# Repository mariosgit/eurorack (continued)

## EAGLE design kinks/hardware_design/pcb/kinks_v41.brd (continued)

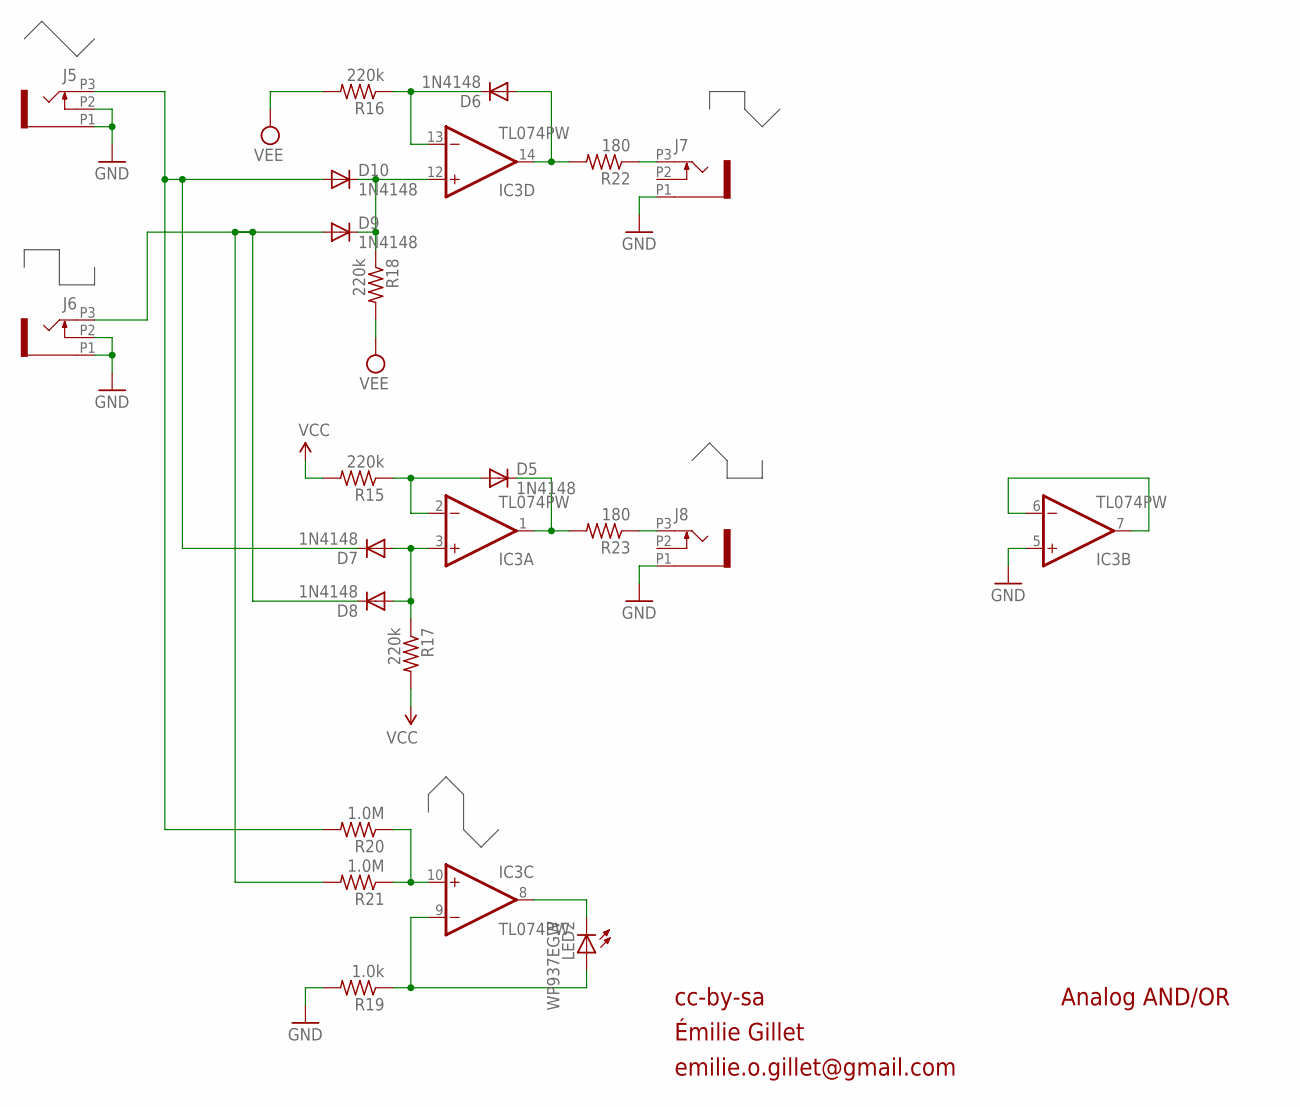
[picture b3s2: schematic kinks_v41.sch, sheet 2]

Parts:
D5, D6, D7, D8, D9, D10: 1N4148; SOD523
IC3: TL074PW; TSSOP14
J5, J6, J7, J8: PJ301_THONKICONN6; WQP_PJ_301M6
LED2: WP937EGW; LED3MM
R15, R16, R17, R18: 220k; R0402
R19: 1.0k; R0402
R20, R21: 1.0M; R0402
R22, R23: 180; R0402

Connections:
A: D7.C, D10.A, J5.P3 (3), R20.2
B: D8.C, D9.A, J6.P3 (3), R21.2
GND: IC3.5 (+IN), J5.P1 (1), J5.P2 (2), J6.P1 (1), J6.P2 (2), J7.P1 (1), J8.P1 (1), R19.2; also elsewhere on the board
unnamed: D9.C, D10.C, IC3.12 (+IN), R18.1
unnamed: D6.A, IC3.14 (OUT), R22.2
unnamed: D6.C, IC3.13 (-IN), R16.1
unnamed: D7.A, D8.A, IC3.3 (+IN), R17.1
unnamed: IC3.6 (-IN), IC3.7 (OUT)
unnamed: D5.C, IC3.1 (OUT), R23.2
unnamed: IC3.8 (OUT), LED2.K (C)
unnamed: D5.A, IC3.2 (-IN), R15.1
unnamed: J8.P3 (3), R23.1
unnamed: IC3.10 (+IN), R20.1, R21.1
unnamed: IC3.9 (-IN), LED2.A, R19.1
unnamed: J7.P3 (3), R22.1
VCC: R15.2, R17.2; also elsewhere on the board
VEE: R16.2, R18.2; also elsewhere on the board

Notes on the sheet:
cc-by-sa
Analog AND/OR
Émilie Gillet
emilie.o.gillet@gmail.com

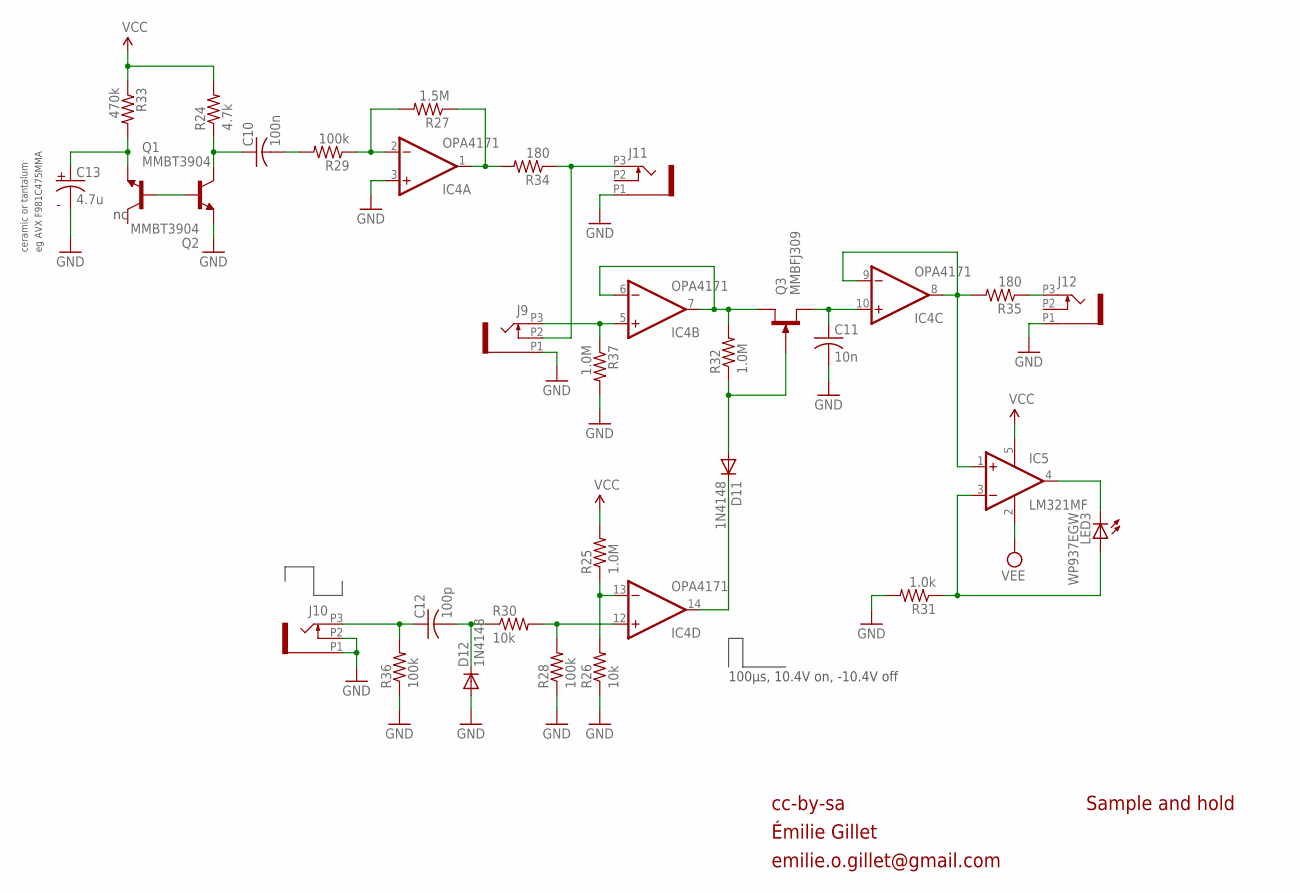
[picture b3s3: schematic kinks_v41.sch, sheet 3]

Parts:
C10: 100n; C0402
C11: 10n; C0603
C12: 100p; C0402
C13: 4.7u; C0603
D11, D12: 1N4148; SOD523
IC4: OPA4171; TSSOP14
IC5: LM321MF; SOT23-5
J9, J10, J11, J12: PJ301_THONKICONN6; WQP_PJ_301M6
LED3: WP937EGW; LED3MM
Q1, Q2: MMBT3904; SOT23-BEC
Q3: MMBFJ309; SOT23
R24: 4.7k; R0402
R25, R32, R37: 1.0M; R0402
R26, R30: 10k; R0402
R27: 1.5M; R0402
R28, R29, R36: 100k; R0402
R31: 1.0k; R0402
R33: 470k; R0402
R34, R35: 180; R0402

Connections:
GND: C11.2, C13.2, D12.A, IC4.3 (+IN), J9.P1 (1), J10.P1 (1), J10.P2 (2), J11.P1 (1), J12.P1 (1), Q1.E, R26.1, R28.1, R31.2, R36.1, R37.2; also elsewhere on the board
unnamed: IC4.8 (OUT), IC4.9 (-IN), IC5.1 (+IN), R35.2
unnamed: Q1.B, Q2.B
unnamed: C13.1, Q2.E, R33.2
unnamed: C10.2, R29.2
unnamed: IC4.2 (-IN), R27.2, R29.1
unnamed: IC5.3 (-IN), LED3.A, R31.1
unnamed: IC5.4 (OUT), LED3.K (C)
unnamed: C10.1, Q1.C, R24.1
unnamed: IC4.1 (OUT), R27.1, R34.2
unnamed: J9.P2 (2), J11.P3 (3), R34.1
unnamed: IC4.5 (+IN), J9.P3 (3), R37.1
unnamed: IC4.6 (-IN), IC4.7 (OUT), Q3.1 (D), R32.2
unnamed: D11.A, Q3.3 (G), R32.1
unnamed: D11.C, IC4.14 (OUT)
unnamed: C11.1, IC4.10 (+IN), Q3.2 (S)
unnamed: IC4.12 (+IN), R28.2, R30.2
unnamed: J12.P3 (3), R35.1
unnamed: C12.1, J10.P3 (3), R36.2
unnamed: IC4.13 (-IN), R25.1, R26.2
unnamed: C12.2, D12.C, R30.1
VCC: IC5.5 (V+), R24.2, R25.2, R33.1; also elsewhere on the board
VEE: IC5.2 (V-); also elsewhere on the board

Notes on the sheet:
cc-by-sa
Sample and hold
100µs, 10.4V on, -10.4V off
eg AVX F981C475MMA
ceramic or tantalum
Émilie Gillet
emilie.o.gillet@gmail.com

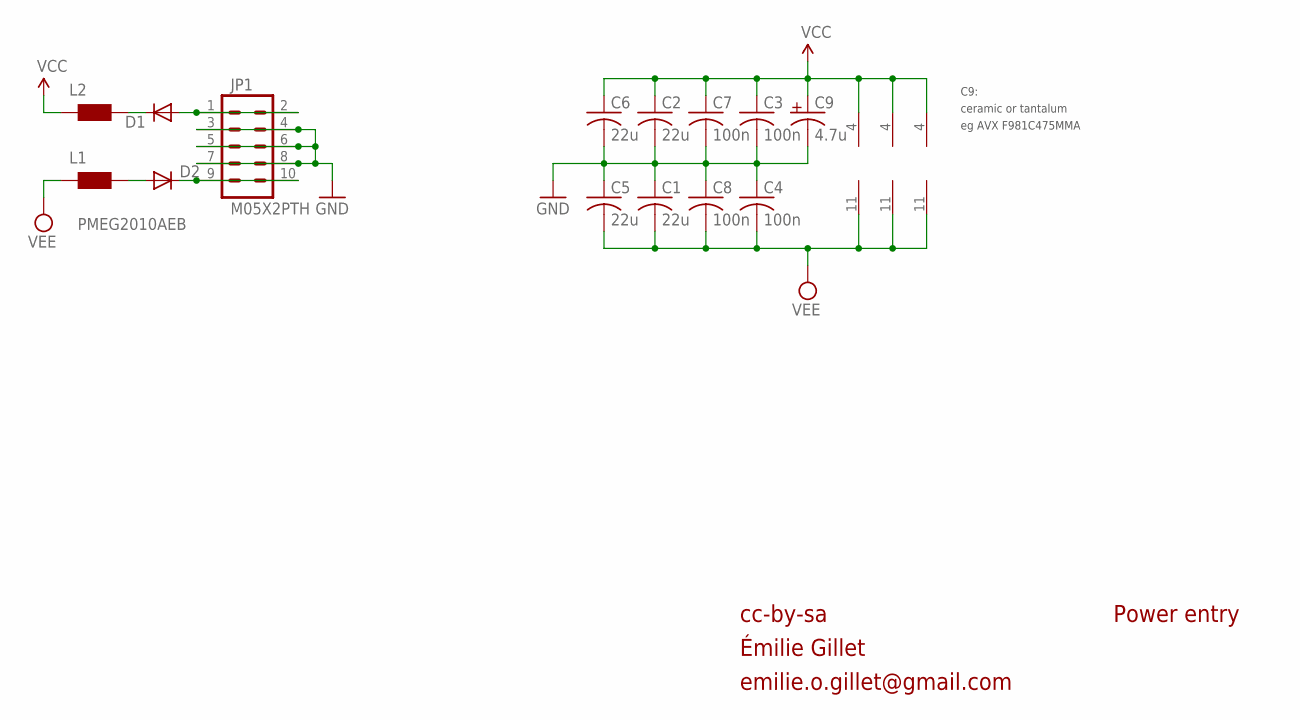
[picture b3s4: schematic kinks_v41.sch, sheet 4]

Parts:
C1, C2, C5, C6: 22u; C0805
C3, C4, C7, C8: 100n; C0402
C9: 4.7u; C0603
D1, D2: PMEG2010AEB; SOD523
IC1, IC3: TL074PW; TSSOP14
IC4: OPA4171; TSSOP14
JP1: M05X2PTH; AVR_ICSP
L1, L2: WE-CBF_0603; 0603

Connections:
GND: C1.1, C2.2, C3.2, C4.1, C5.1, C6.2, C7.2, C8.1, C9.2, JP1.3, JP1.4, JP1.5, JP1.6, JP1.7, JP1.8; also elsewhere on the board
unnamed: D1.A, JP1.1, JP1.2
unnamed: D2.C, JP1.9, JP1.10
unnamed: D1.C, L2.2
unnamed: D2.A, L1.2
VCC: C2.1, C3.1, C6.1, C7.1, C9.1, IC1.4 (V+), IC3.4 (V+), IC4.4 (V+), L2.1; also elsewhere on the board
VEE: C1.2, C4.2, C5.2, C8.2, IC1.11 (V-), IC3.11 (V-), IC4.11 (V-), L1.1; also elsewhere on the board

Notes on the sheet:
cc-by-sa
Power entry
eg AVX F981C475MMA
ceramic or tantalum
C9:
Émilie Gillet
emilie.o.gillet@gmail.com

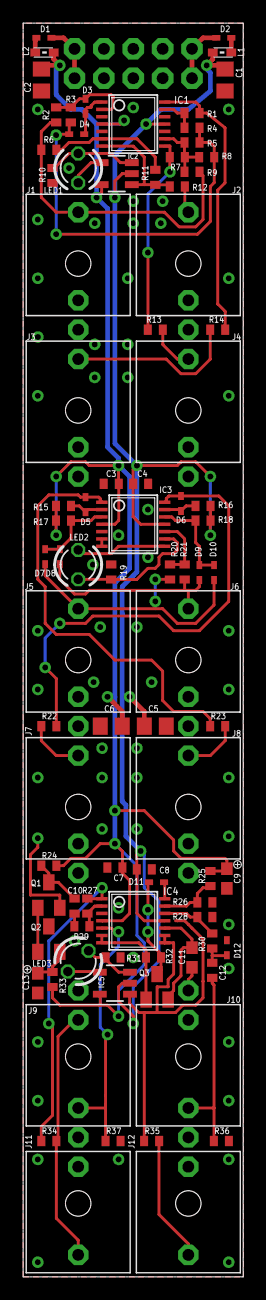
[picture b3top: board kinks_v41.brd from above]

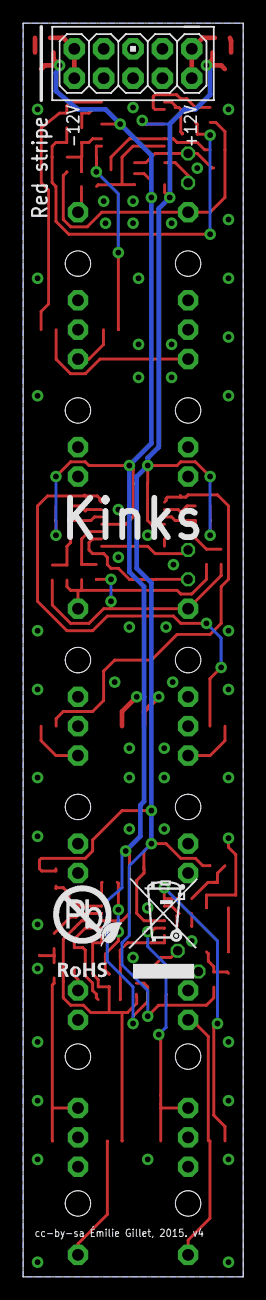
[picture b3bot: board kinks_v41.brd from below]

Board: 2 copper layers, 19.0 x 108.4 mm, 89 parts (2 on the bottom side), 56 nets.

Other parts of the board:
U$2: ROHS

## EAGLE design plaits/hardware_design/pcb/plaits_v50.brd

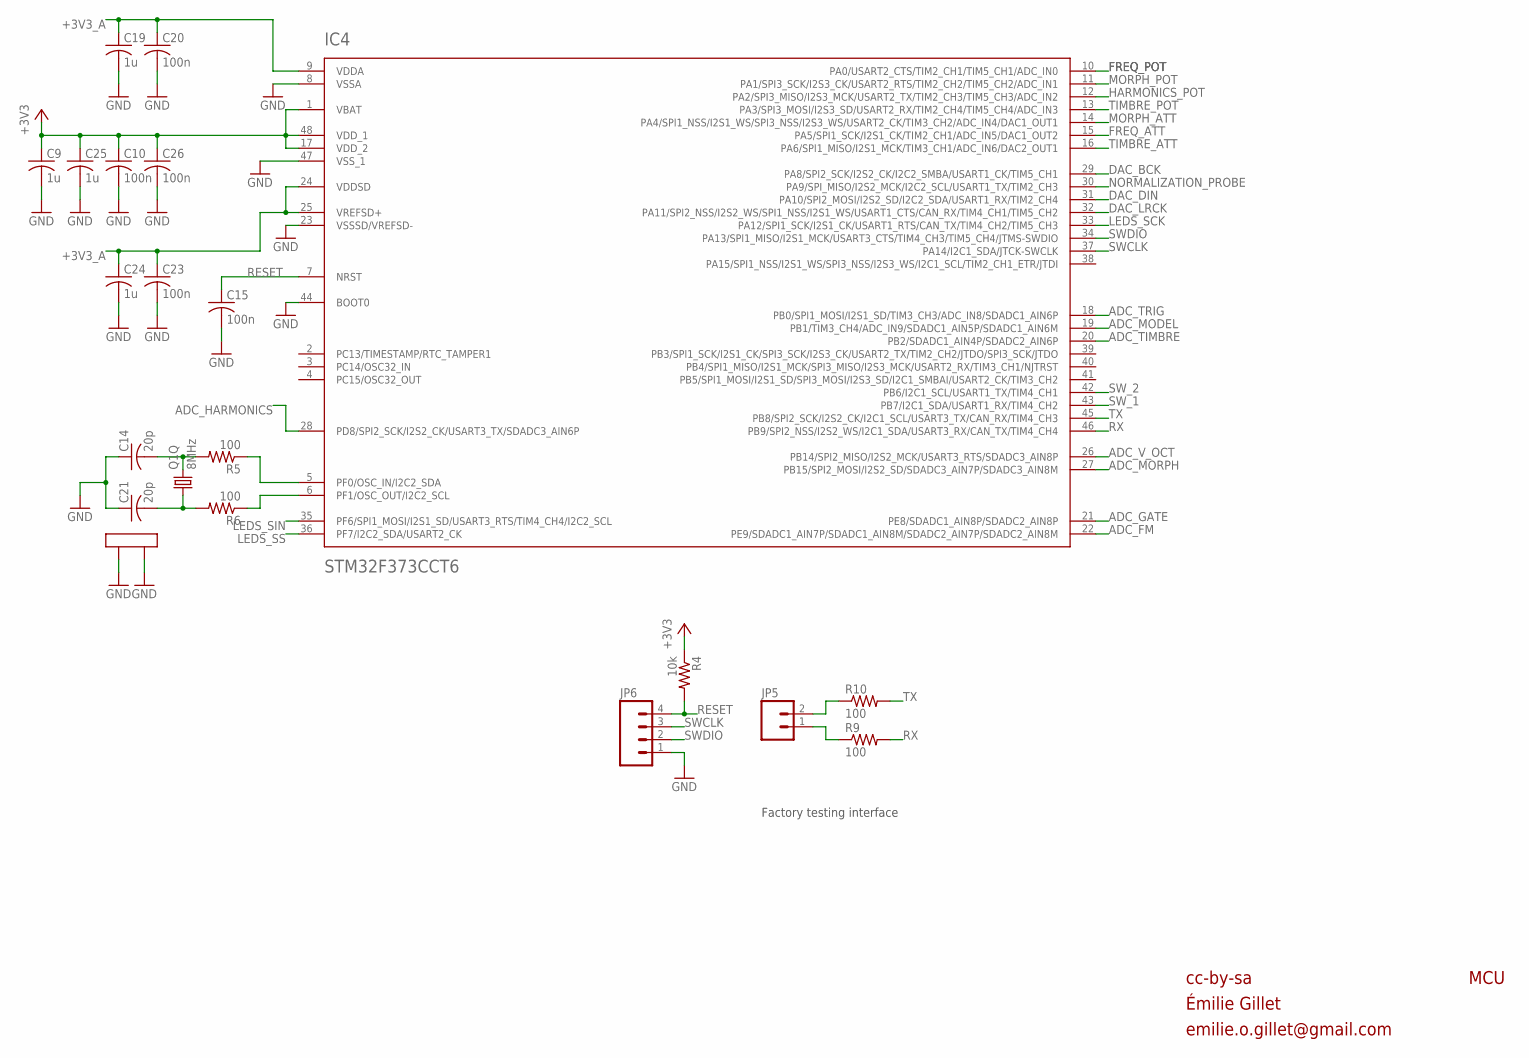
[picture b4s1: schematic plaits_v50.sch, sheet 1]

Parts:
C9, C19, C24, C25: 1u; C0603
C10, C15, C20, C23, C26: 100n; C0603
C14, C21: 20p; C0603
IC4: STM32F373CCT6; LQFP48
JP5: M02PTH; 1X02
JP6: M04PTH; 1X04
Q1: 8MHz; CTS406
R4: 10k; R0603
R5, R6, R9, R10: 100; R0603

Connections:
+3V3: C9.1, C10.1, C25.1, C26.1, IC4.1 (VBAT), IC4.17 (VDD_2), IC4.48 (VDD_1), R4.1; also elsewhere on the board
+3V3_A: C19.1, C20.1, C23.1, C24.1, IC4.9 (VDDA), IC4.24 (VDDSD), IC4.25 (VREFSD+); also elsewhere on the board
ADC_FM: IC4.22 (PE9/SDADC1_AIN7P/SDADC1_AIN8M/SDADC2_AI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); also elsewhere on the board
ADC_GATE: IC4.21 (PE8/SDADC1_AIN8P/SDADC2_AIN8P); also elsewhere on the board
ADC_HARMONICS: IC4.28 (PD8/SPI2_SCK/I2S2_CK/USART3_TX/SDADC3_A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); also elsewhere on the board
ADC_MODEL: IC4.19 (PB1/TIM3_CH4/ADC_IN9/SDADC1_AIN5P/SDADC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); also elsewhere on the board
ADC_MORPH: IC4.27 (PB15/SPI2_MOSI/I2S2_SD/SDADC3_AIN7P/SDA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); also elsewhere on the board
ADC_TIMBRE: IC4.20 (PB2/SDADC1_AIN4P/SDADC2_AIN6P); also elsewhere on the board
ADC_TRIG: IC4.18 (PB0/SPI1_MOSI/I2S1_SD/TIM3_CH3/ADC_IN8/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); also elsewhere on the board
ADC_V_OCT: IC4.26 (PB14/SPI2_MISO/I2S2_MCK/USART3_RTS/SDAD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); also elsewhere on the board
DAC_BCK: IC4.29 (PA8/SPI2_SCK/I2S2_CK/I2C2_SMBA/USART1_C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); also elsewhere on the board
DAC_DIN: IC4.31 (PA10/SPI2_MOSI/I2S2_SD/I2C2_SDA/USART1_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); also elsewhere on the board
DAC_LRCK: IC4.32 (PA11/SPI2_NSS/I2S2_WS/SPI1_NSS/I2S1_WS/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); also elsewhere on the board
FREQ_ATT: IC4.15 (PA5/SPI1_SCK/I2S1_CK/TIM2_CH1/ADC_IN5/D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); also elsewhere on the board
FREQ_POT: IC4.10 (PA0/USART2_CTS/TIM2_CH1/TIM5_CH1/ADC_IN0); also elsewhere on the board
GND: C9.2, C10.2, C14.1, C15.2, C19.2, C20.2, C21.1, C23.2, C24.2, C25.2, C26.2, IC4.8 (VSSA), IC4.23 (VSSSD/VREFSD-), IC4.44 (BOOT0), IC4.47 (VSS_1), JP6.1, Q1.2 (LID1), Q1.4 (LID2); also elsewhere on the board
HARMONICS_POT: IC4.12 (PA2/SPI3_MISO/I2S3_MCK/USART2_TX/TIM2_C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); also elsewhere on the board
LEDS_SCK: IC4.33 (PA12/SPI1_SCK/I2S1_CK/USART1_RTS/CAN_TX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); also elsewhere on the board
LEDS_SIN: IC4.35 (PF6/SPI1_MOSI/I2S1_SD/USART3_RTS/TIM4_C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); also elsewhere on the board
LEDS_SS: IC4.36 (PF7/I2C2_SDA/USART2_CK); also elsewhere on the board
MORPH_ATT: IC4.14 (PA4/SPI1_NSS/I2S1_WS/SPI3_NSS/I2S3_WS/U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); also elsewhere on the board
MORPH_POT: IC4.11 (PA1/SPI3_SCK/I2S3_CK/USART2_RTS/TIM2_CH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); also elsewhere on the board
unnamed: IC4.5 (PF0/OSC_IN/I2C2_SDA), R5.1
unnamed: IC4.6 (PF1/OSC_OUT/I2C2_SCL), R6.1
unnamed: C14.2, Q1.3 (2), R5.2
unnamed: JP5.2, R10.1
unnamed: C21.2, Q1.1, R6.2
unnamed: JP5.1, R9.1
NORMALIZATION_PROBE: IC4.30 (PA9/SPI_MISO/I2S2_MCK/I2C2_SCL/USART1_T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); also elsewhere on the board
RESET: C15.1, IC4.7 (NRST), JP6.4, R4.2
RX: IC4.46 (PB9/SPI2_NSS/I2S2_WS/I2C1_SDA/USART3_RX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), R9.2
SWCLK: IC4.37 (PA14/I2C1_SDA/JTCK-SWCLK), JP6.3
SWDIO: IC4.34 (PA13/SPI1_MISO/I2S1_MCK/USART3_CTS/TIM4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), JP6.2
SW_1: IC4.43 (PB7/I2C1_SDA/USART1_RX/TIM4_CH2); also elsewhere on the board
SW_2: IC4.42 (PB6/I2C1_SCL/USART1_TX/TIM4_CH1); also elsewhere on the board
TIMBRE_ATT: IC4.16 (PA6/SPI1_MISO/I2S1_MCK/TIM3_CH1/ADC_IN6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); also elsewhere on the board
TIMBRE_POT: IC4.13 (PA3/SPI3_MOSI/I2S3_SD/USART2_RX/TIM2_CH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); also elsewhere on the board
TX: IC4.45 (PB8/SPI2_SCK/I2S2_CK/I2C1_SCL/USART3_TX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), R10.2

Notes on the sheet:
cc-by-sa
MCU
Factory testing interface
Émilie Gillet
emilie.o.gillet@gmail.com

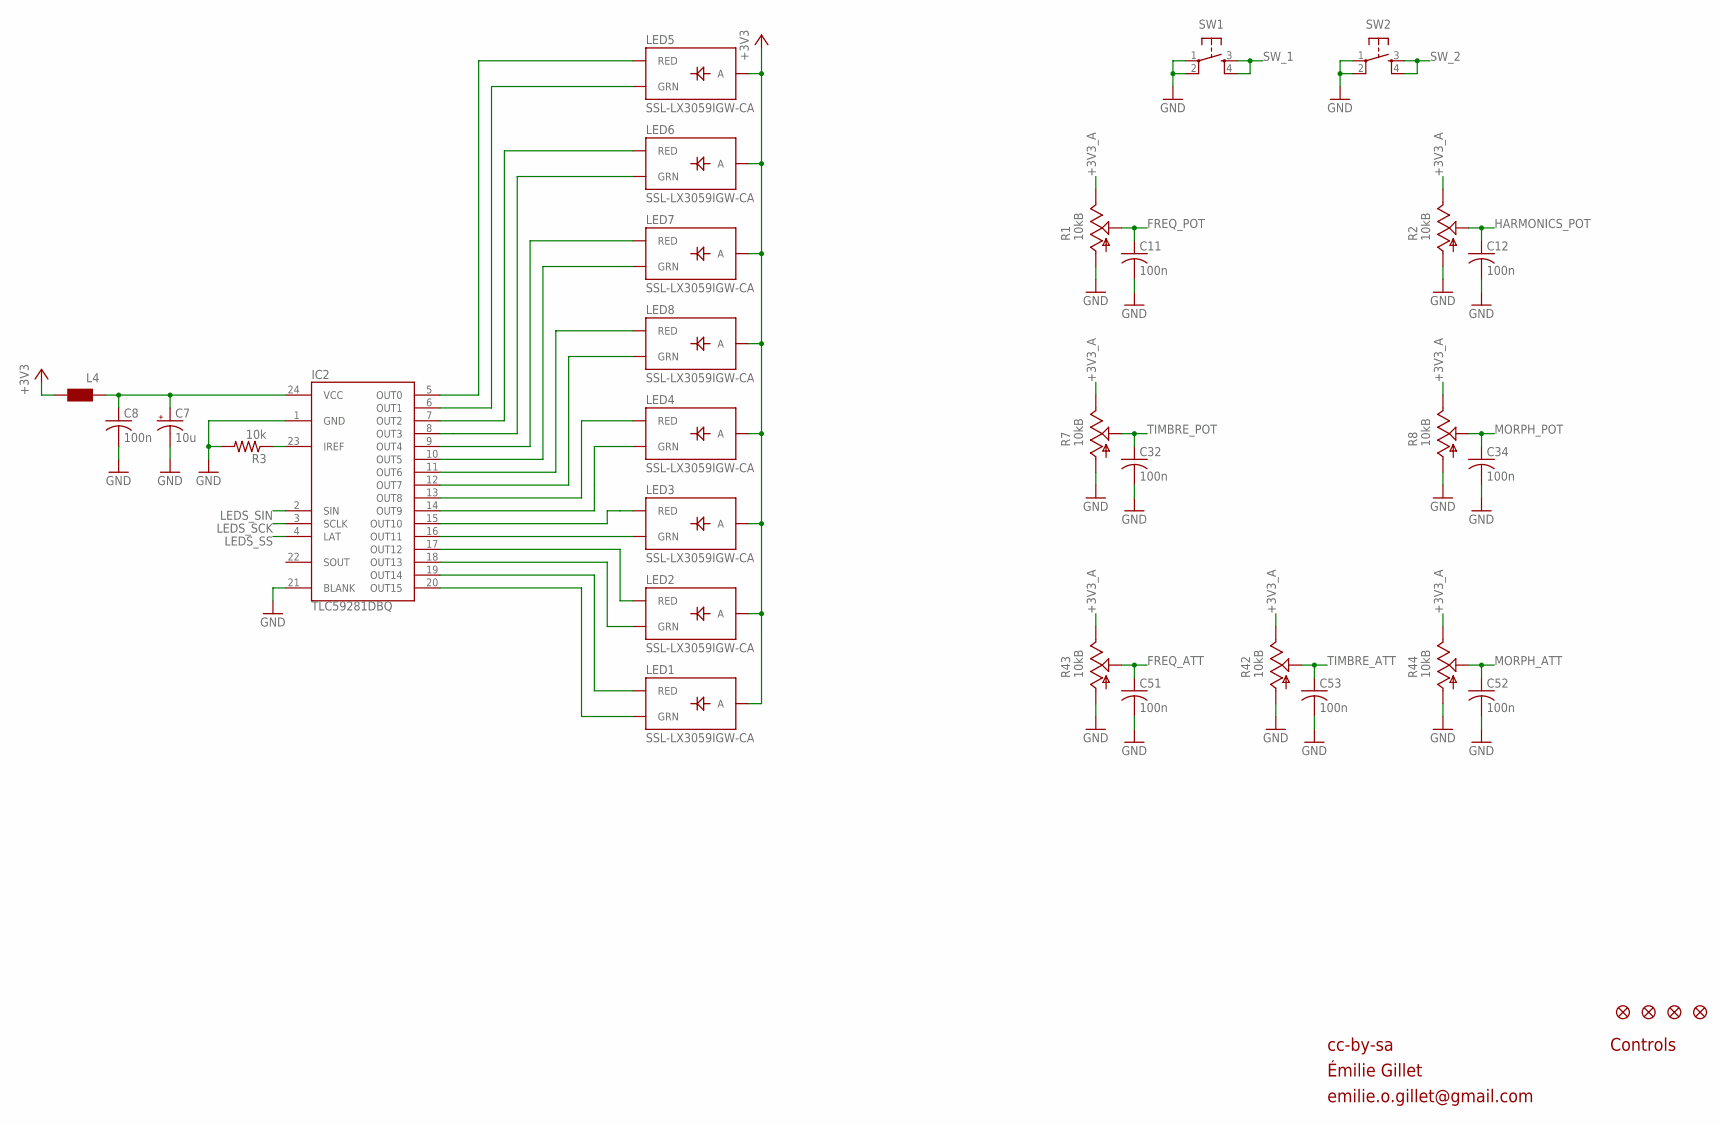
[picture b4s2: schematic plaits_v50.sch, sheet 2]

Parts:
C7: 10u; PANASONIC_A
C8, C11, C12, C32, C34, C51, C52, C53: 100n; C0603
IC2: TLC59281DBQ; TSSOP24_0635
JP1, JP2, JP3, JP4: FIDUCIAL1X2; FIDUCIAL-1X2
L4: WE-CBF_0603; 0603
LED1, LED2, LED3, LED4, LED5, LED6, LED7, LED8: SSL-LX3059IGW-CA; LED-BICOLOR-THROUGHHOLE-LUMEX
R1, R2, R7, R8: 10kB; ALPS_POT_VERTICAL_PS
R3: 10k; R0603
R42, R43, R44: 10kB; ALPS_POT_VERTICAL
SW1, SW2: TAC_SWITCHPTH; TACTILE-PTH

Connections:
+3V3: L4.2, LED1.A, LED2.A, LED3.A, LED4.A, LED5.A, LED6.A, LED7.A, LED8.A; also elsewhere on the board
+3V3_A: R1.P$1 (E), R2.P$1 (E), R7.P$1 (E), R8.P$1 (E), R42.P$1 (E), R43.P$1 (E), R44.P$1 (E); also elsewhere on the board
FREQ_ATT: C51.1, R43.P$2 (S); also elsewhere on the board
FREQ_POT: C11.1, R1.P$2 (S); also elsewhere on the board
GND: C7.-, C8.2, C11.2, C12.2, C32.2, C34.2, C51.2, C52.2, C53.2, IC2.1 (GND), IC2.21 (BLANK), R1.P$3 (A), R2.P$3 (A), R3.2, R7.P$3 (A), R8.P$3 (A), R42.P$3 (A), R43.P$3 (A), R44.P$3 (A), SW1.1, SW1.2, SW2.1, SW2.2; also elsewhere on the board
HARMONICS_POT: C12.1, R2.P$2 (S); also elsewhere on the board
LEDS_SCK: IC2.3 (SCLK); also elsewhere on the board
LEDS_SIN: IC2.2 (SIN); also elsewhere on the board
LEDS_SS: IC2.4 (LAT); also elsewhere on the board
MORPH_ATT: C52.1, R44.P$2 (S); also elsewhere on the board
MORPH_POT: C34.1, R8.P$2 (S); also elsewhere on the board
unnamed: IC2.12 (OUT7), LED8.GREEN_C (GRN)
unnamed: IC2.11 (OUT6), LED8.RED_C (RED)
unnamed: IC2.10 (OUT5), LED7.GREEN_C (GRN)
unnamed: IC2.9 (OUT4), LED7.RED_C (RED)
unnamed: IC2.8 (OUT3), LED6.GREEN_C (GRN)
unnamed: IC2.13 (OUT8), LED4.RED_C (RED)
unnamed: IC2.7 (OUT2), LED6.RED_C (RED)
unnamed: IC2.14 (OUT9), LED4.GREEN_C (GRN)
unnamed: IC2.6 (OUT1), LED5.GREEN_C (GRN)
unnamed: IC2.15 (OUT10), LED3.RED_C (RED)
unnamed: IC2.16 (OUT11), LED3.GREEN_C (GRN)
unnamed: IC2.17 (OUT12), LED2.RED_C (RED)
unnamed: IC2.18 (OUT13), LED2.GREEN_C (GRN)
unnamed: IC2.19 (OUT14), LED1.RED_C (RED)
unnamed: IC2.5 (OUT0), LED5.RED_C (RED)
unnamed: IC2.20 (OUT15), LED1.GREEN_C (GRN)
unnamed: C7.+, C8.1, IC2.24 (VCC), L4.1
unnamed: IC2.23 (IREF), R3.1
SW_1: SW1.3, SW1.4; also elsewhere on the board
SW_2: SW2.3, SW2.4; also elsewhere on the board
TIMBRE_ATT: C53.1, R42.P$2 (S); also elsewhere on the board
TIMBRE_POT: C32.1, R7.P$2 (S); also elsewhere on the board

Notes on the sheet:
cc-by-sa
Controls
Émilie Gillet
emilie.o.gillet@gmail.com

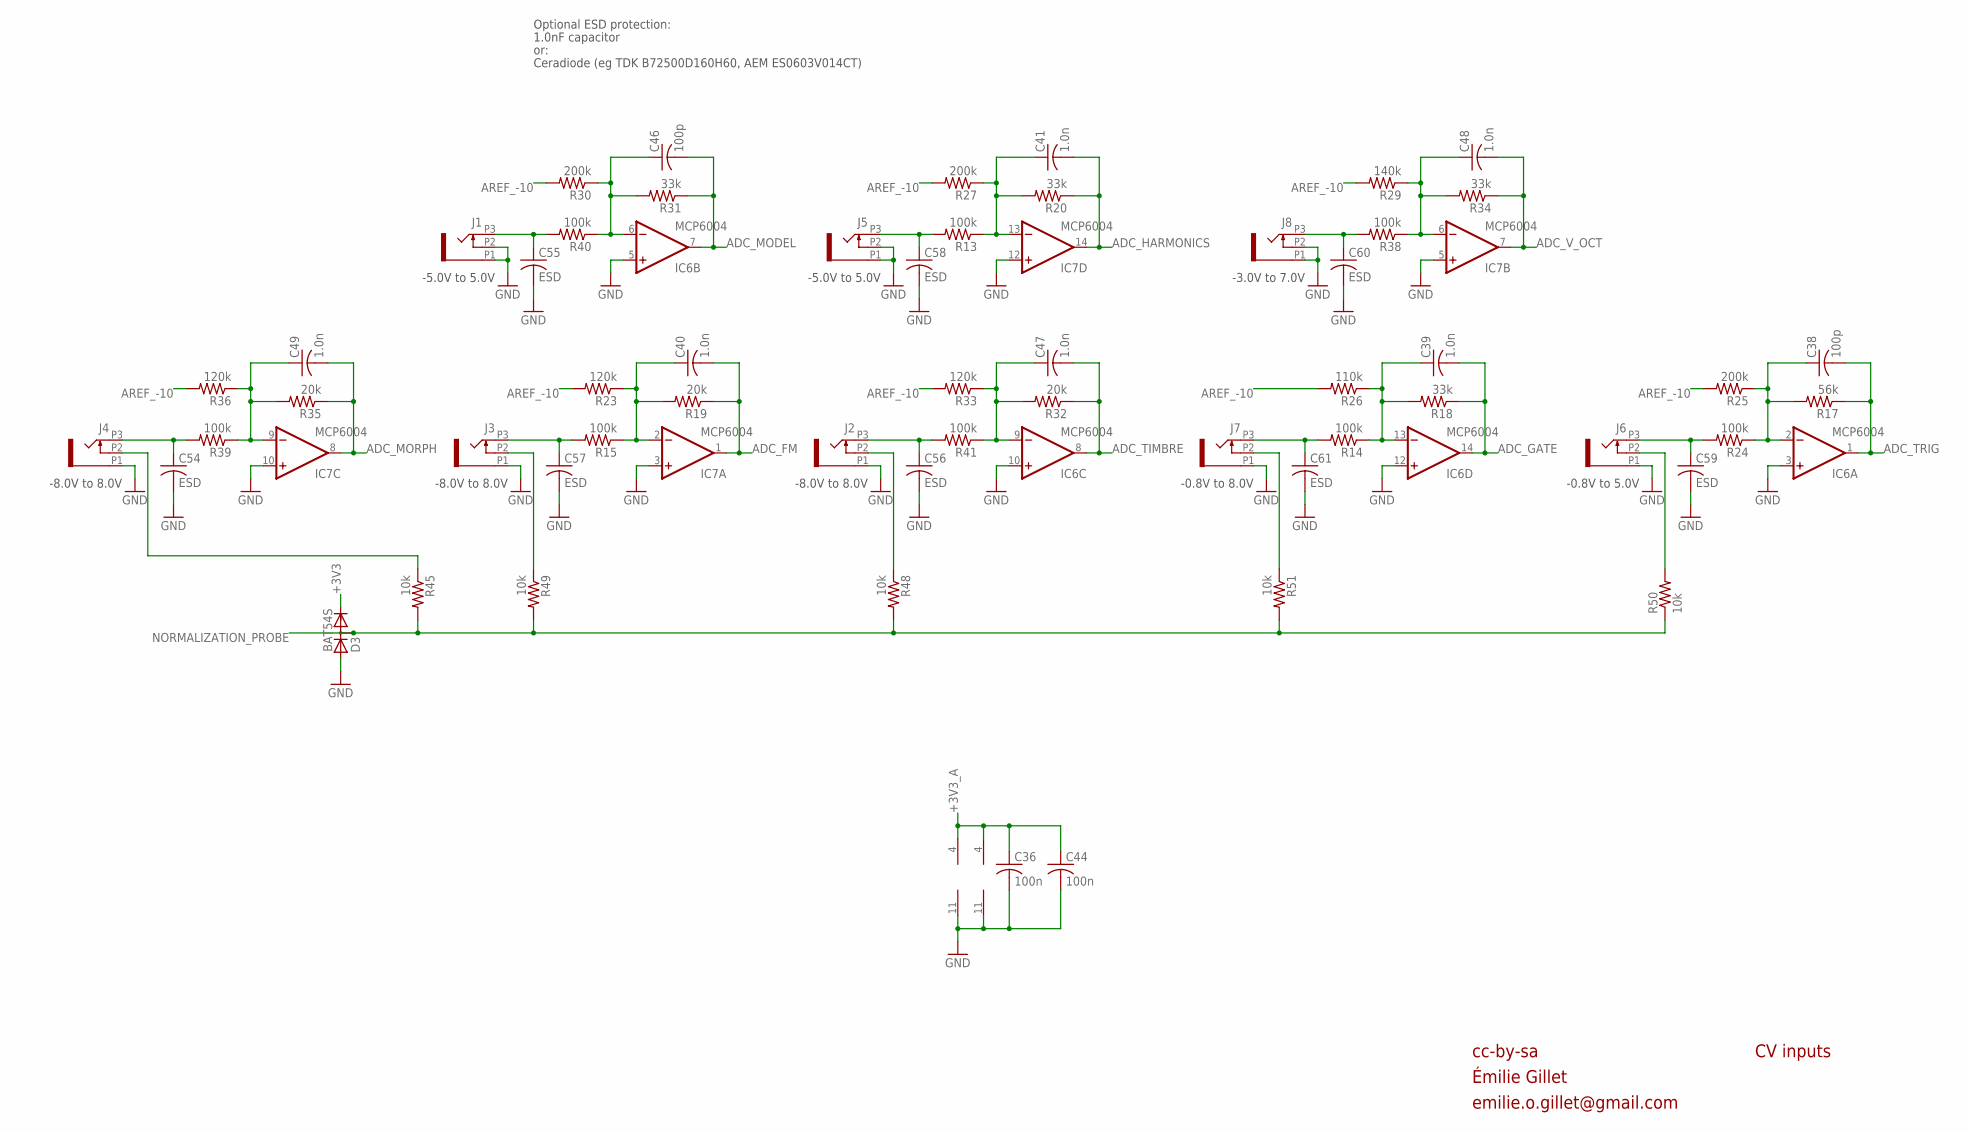
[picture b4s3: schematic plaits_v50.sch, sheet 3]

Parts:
C36, C44: 100n; C0603
C38, C46: 100p; C0603
C39, C40, C41, C47, C48, C49: 1.0n; C0603
C54, C55, C56, C57, C58, C59, C60, C61: ESD; C0603
D3: BAT54S; SOT23
IC6, IC7: MCP6004; TSSOP14_065
J1, J2, J3, J4, J5, J6, J7, J8: PJ301_THONKICONN6; WQP_PJ_301M6
R13, R14, R15, R24, R38, R39, R40, R41: 100k; R0603
R17: 56k; R0603
R18, R20, R31, R34: 33k; R0603
R19, R32, R35: 20k; R0603
R23, R33, R36: 120k; R0603
R25, R27, R30: 200k; R0603
R26: 110k; R0603
R29: 140k; R0603
R45, R48, R49, R50, R51: 10k; R0603

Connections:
+3V3: D3.2 (C); also elsewhere on the board
+3V3_A: C36.1, C44.1, IC6.4 (V+), IC7.4 (V+); also elsewhere on the board
ADC_FM: C40.2, IC7.1 (OUT), R19.1; also elsewhere on the board
ADC_GATE: C39.2, IC6.14 (OUT), R18.1; also elsewhere on the board
ADC_HARMONICS: C41.2, IC7.14 (OUT), R20.1; also elsewhere on the board
ADC_MODEL: C46.2, IC6.7 (OUT), R31.1; also elsewhere on the board
ADC_MORPH: C49.2, IC7.8 (OUT), R35.1; also elsewhere on the board
ADC_TIMBRE: C47.2, IC6.8 (OUT), R32.1; also elsewhere on the board
ADC_TRIG: C38.2, IC6.1 (OUT), R17.1; also elsewhere on the board
ADC_V_OCT: C48.2, IC7.7 (OUT), R34.1; also elsewhere on the board
AREF_-10: R23.2, R25.2, R26.2, R27.2, R29.2, R30.2, R33.2, R36.2; also elsewhere on the board
FM_IN: C57.1, J3.P3 (3), R15.2
GATE_IN: C61.1, J7.P3 (3), R14.2
GATE_IN1: C59.1, J6.P3 (3), R24.2
GND: C36.2, C44.2, C54.2, C55.2, C56.2, C57.2, C58.2, C59.2, C60.2, C61.2, D3.1 (A), IC6.3 (+IN), IC6.5 (+IN), IC6.10 (+IN), IC6.11 (V-), IC6.12 (+IN), IC7.3 (+IN), IC7.5 (+IN), IC7.10 (+IN), IC7.11 (V-), IC7.12 (+IN), J1.P1 (1), J1.P2 (2), J2.P1 (1), J3.P1 (1), J4.P1 (1), J5.P1 (1), J5.P2 (2), J6.P1 (1), J7.P1 (1), J8.P1 (1), J8.P2 (2); also elsewhere on the board
HARMONICS_IN: C58.1, J5.P3 (3), R13.2
MODEL_IN: C55.1, J1.P3 (3), R40.2
MORPH_IN: C54.1, J4.P3 (3), R39.2
unnamed: J6.P2 (2), R50.2
unnamed: C38.1, IC6.2 (-IN), R17.2, R24.1, R25.1
unnamed: J3.P2 (2), R49.1
unnamed: J2.P2 (2), R48.1
unnamed: J4.P2 (2), R45.1
unnamed: C39.1, IC6.13 (-IN), R14.1, R18.2, R26.1
unnamed: C48.1, IC7.6 (-IN), R29.1, R34.2, R38.1
unnamed: C56.1, J2.P3 (3), R41.2
unnamed: C49.1, IC7.9 (-IN), R35.2, R36.1, R39.1
unnamed: C40.1, IC7.2 (-IN), R15.1, R19.2, R23.1
unnamed: J7.P2 (2), R51.1
unnamed: C46.1, IC6.6 (-IN), R30.1, R31.2, R40.1
unnamed: C47.1, IC6.9 (-IN), R32.2, R33.1, R41.1
unnamed: C41.1, IC7.13 (-IN), R13.1, R20.2, R27.1
NORMALIZATION_PROBE: D3.3 (AC), R45.2, R48.2, R49.2, R50.1, R51.2; also elsewhere on the board
V_OCT_IN: C60.1, J8.P3 (3), R38.2

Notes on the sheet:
cc-by-sa
CV inputs
-3.0V to 7.0V
-8.0V to 8.0V
-5.0V to 5.0V
-0.8V to 8.0V
-0.8V to 5.0V
Optional ESD protection:
1.0nF capacitor
or:
Ceradiode (eg TDK B72500D160H60, AEM ES0603V014CT)
Émilie Gillet
emilie.o.gillet@gmail.com

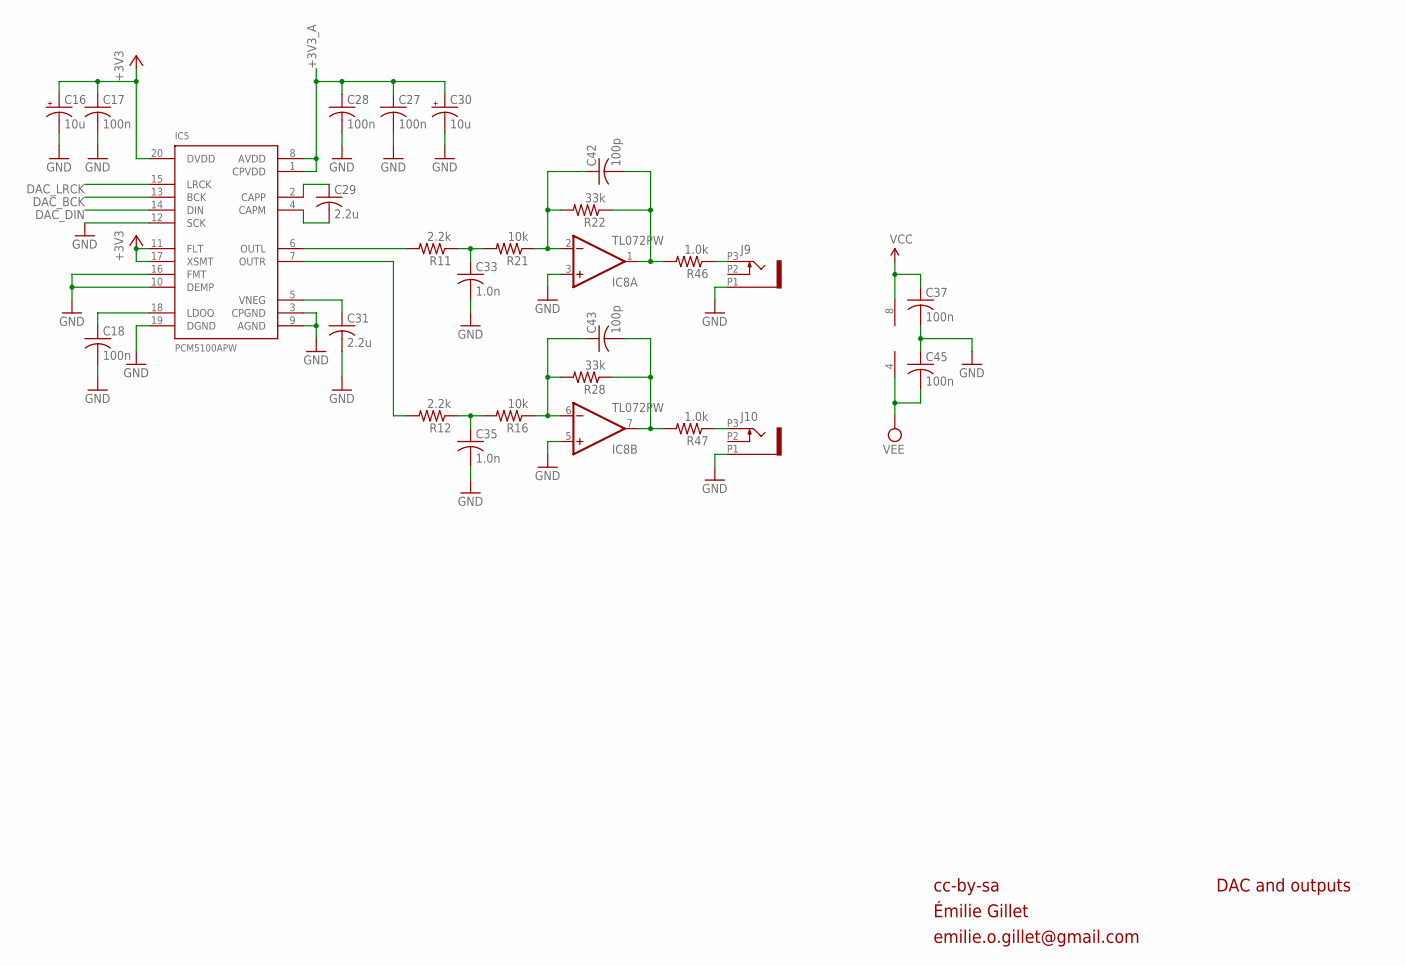
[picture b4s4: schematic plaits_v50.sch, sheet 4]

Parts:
C16, C30: 10u; PANASONIC_A
C17, C18, C27, C28, C37, C45: 100n; C0603
C29, C31: 2.2u; C0805
C33, C35: 1.0n; C0603
C42, C43: 100p; C0603
IC5: PCM5100APW; SSOP20
IC8: TL072PW; TSSOP08
J9, J10: PJ301_THONKICONN6; WQP_PJ_301M6
R11, R12: 2.2k; R0603
R16, R21: 10k; R0603
R22, R28: 33k; R0603
R46, R47: 1.0k; R0603

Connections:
+3V3: C16.+, C17.1, IC5.11 (FLT), IC5.17 (XSMT), IC5.20 (DVDD); also elsewhere on the board
+3V3_A: C27.1, C28.1, C30.+, IC5.1 (CPVDD), IC5.8 (AVDD); also elsewhere on the board
DAC_BCK: IC5.13 (BCK); also elsewhere on the board
DAC_DIN: IC5.14 (DIN); also elsewhere on the board
DAC_LRCK: IC5.15 (LRCK); also elsewhere on the board
GND: C16.-, C17.2, C18.2, C27.2, C28.2, C30.-, C31.2, C33.2, C35.2, C37.2, C45.1, IC5.3 (CPGND), IC5.9 (AGND), IC5.10 (DEMP), IC5.12 (SCK), IC5.16 (FMT), IC5.19 (DGND), IC8.3 (+IN), IC8.5 (+IN), J9.P1 (1), J10.P1 (1); also elsewhere on the board
unnamed: C29.1, IC5.2 (CAPP)
unnamed: C29.2, IC5.4 (CAPM)
unnamed: IC5.6 (OUTL), R11.2
unnamed: C33.1, R11.1, R21.2
unnamed: C35.1, R12.1, R16.2
unnamed: C31.1, IC5.5 (VNEG)
unnamed: C18.1, IC5.18 (LDOO)
unnamed: IC5.7 (OUTR), R12.2
unnamed: C43.1, IC8.6 (-IN), R16.1, R28.2
unnamed: C43.2, IC8.7 (OUT), R28.1, R47.2
unnamed: C42.1, IC8.2 (-IN), R21.1, R22.2
unnamed: C42.2, IC8.1 (OUT), R22.1, R46.2
unnamed: J9.P3 (3), R46.1
unnamed: J10.P3 (3), R47.1
VCC: C37.1, IC8.8 (V+); also elsewhere on the board
VEE: C45.2, IC8.4 (V-); also elsewhere on the board

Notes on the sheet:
cc-by-sa
DAC and outputs
Émilie Gillet
emilie.o.gillet@gmail.com

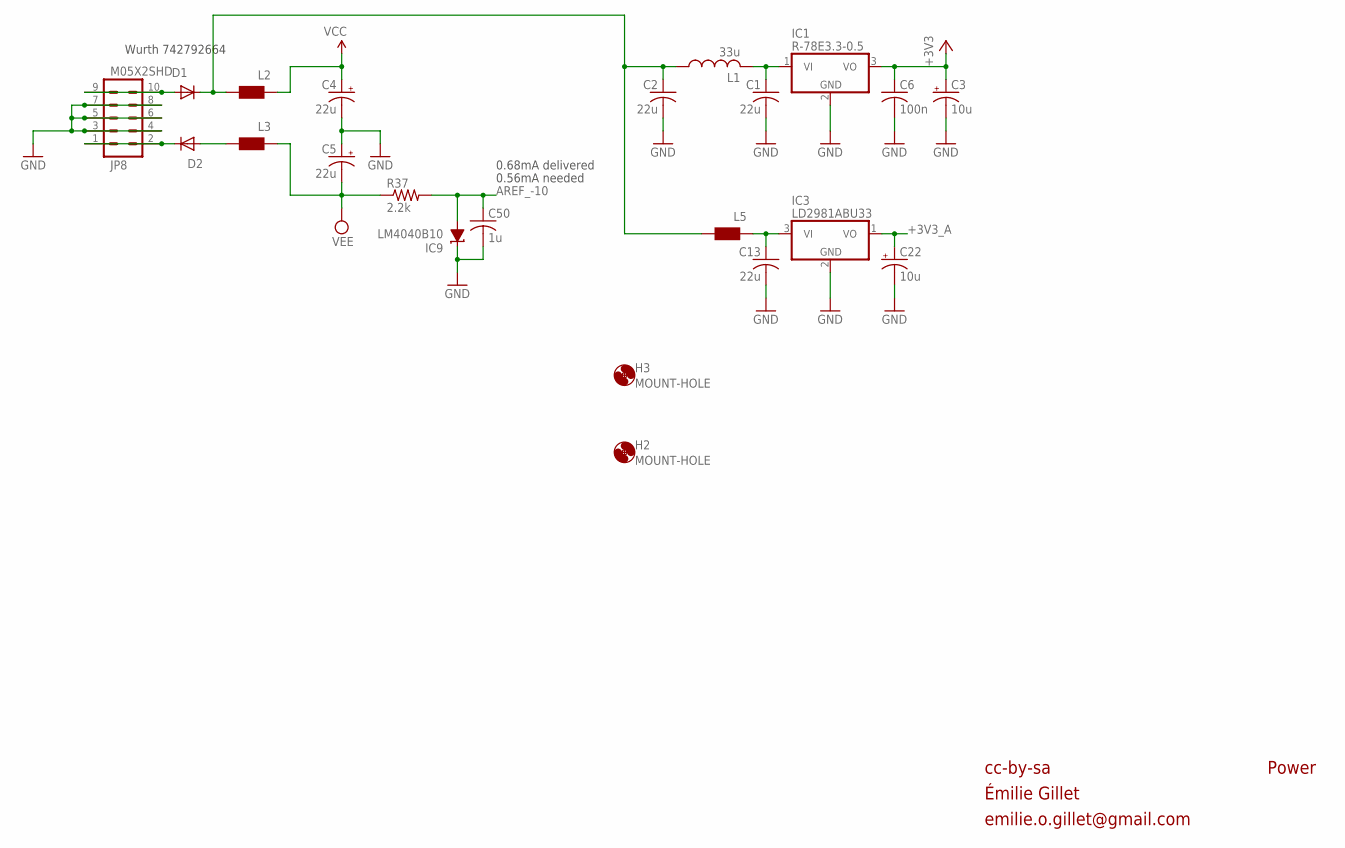
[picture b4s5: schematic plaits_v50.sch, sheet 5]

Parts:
C1, C2, C13: 22u; C1206
C3, C22: 10u; PANASONIC_A
C4, C5: 22u; PANASONIC_B
C6: 100n; C0603
C50: 1u; C0603
D1, D2: 1N5819HW; SOD123
H2, H3: MOUNT-HOLE; 3,0TINY
IC1: R-78E3.3-0.5; WE78
IC3: LD2981ABU33; SOT89
IC9: LM4040B10; DBZ_R-PDSO-G3
JP8: M05X2SHD; 2X5-SHROUDED
L1: 33u; L2012C
L2, L3, L5: WE-CBF_0603; 0603
R37: 2.2k; R0603

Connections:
+3V3: C3.+, C6.1, IC1.3 (VO); also elsewhere on the board
+3V3_A: C22.+, IC3.1 (VO); also elsewhere on the board
AREF_-10: C50.1, IC9.2 (A), R37.2; also elsewhere on the board
GND: C1.2, C2.2, C3.-, C4.-, C5.+, C6.2, C13.2, C22.-, C50.2, IC1.2 (GND), IC3.2 (GND), IC9.1 (C), JP8.3, JP8.4, JP8.5, JP8.6, JP8.7, JP8.8; also elsewhere on the board
unnamed: C1.1, IC1.1 (VI), L1.2
unnamed: D2.A, L3.2
unnamed: C2.1, D1.C, L1.1, L2.2, L5.2
unnamed: C13.1, IC3.3 (VI), L5.1
unnamed: D1.A, JP8.9, JP8.10
unnamed: D2.C, JP8.1, JP8.2
VCC: C4.+, L2.1; also elsewhere on the board
VEE: C5.-, L3.1, R37.1; also elsewhere on the board

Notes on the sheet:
cc-by-sa
Power
0.56mA needed
Wurth 742792664
0.68mA delivered
Émilie Gillet
emilie.o.gillet@gmail.com
